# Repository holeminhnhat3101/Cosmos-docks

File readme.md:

# Cosmos Docks

Cosmos Docks is a custom 9-key macropad designed from scratch for Hack Club Stardance. It includes a custom PCB, a fully 3D-printable case, one rotary encoder, an OLED display, and SK6812MINI-E addressable RGB LEDs.

The design is built around the Seeed XIAO RP2040 and uses QMK firmware.

## Features

- 9 MX-style mechanical switches
- 1 EC11 rotary encoder
- 0.91 inch 128×32 I2C OLED display
- 13 SK6812MINI-E addressable RGB LEDs
- Seeed XIAO RP2040 microcontroller
- Custom 2-layer PCB designed in KiCad
- Fully 3D-printable top and bottom case
- QMK firmware with OLED, encoder, and RGB Matrix support
- M3 screws and heat-set inserts for case assembly

### PCB design preview

### PCB Layout

### Schematic

### 3D Assembly

## Bill of Materials

| Component                         | Quantity | Notes                                                              |
| --------------------------------- | -------: | ------------------------------------------------------------------ |
| Seeed XIAO RP2040                 |        1 | Main microcontroller                                               |
| MX-style mechanical switches      |        9 | Main key switches                                                  |
| Blank DSA keycaps                 |        9 | Keycaps for the switches                                           |
| 1N4148W SMD diodes                |        9 | One diode per switch                                               |
| EC11 rotary encoder               |        1 | 20 mm D-shaft rotary encoder                                       |
| 0.91 inch 128×32 I2C OLED display |        1 | OLED screen connected through I2C                                  |
| JST-SH 4-pin connector            |        1 | QWIIC/I2C OLED connector, SM04B-SRSS-TB, 1.00 mm pitch, horizontal |
| SK6812MINI-E RGB LEDs             |       13 | Addressable RGB LEDs                                               |
| 0.1 µF capacitors                 |       13 | One decoupling capacitor per RGB LED                               |
| 10 nF capacitors                  |        2 | Rotary encoder debounce/filtering capacitors                       |
| SN74LV1T34DBV level shifter       |        1 | Shifts LED data from 3.3 V to 5 V                                  |
| 330 Ω resistor                    |        1 | LED data line resistor                                             |
| 10 kΩ resistors                   |        4 | Rotary encoder pull-up/pull-down resistors                         |
| M3×16 mm screws                   |        4 | Used to connect the top and bottom case                            |
| M3 heat-set inserts               |        4 | Installed into the 3D-printed case                                 |
| Custom PCB                        |        1 | 2-layer PCB designed in KiCad                                      |
| 3D-printed top case               |        1 | Top enclosure / switch plate                                       |
| 3D-printed bottom case            |        1 | Bottom enclosure                                                   |
| Soldering equipment               |        1 | I don't have one                                                   |

## Firmware

The firmware is written using QMK. It includes support for:

- 3×3 key matrix
- Rotary encoder
- OLED display
- RGB Matrix lighting for SK6812MINI-E LEDs

The compiled firmware file is included in the production folder as:

firmware.uf2

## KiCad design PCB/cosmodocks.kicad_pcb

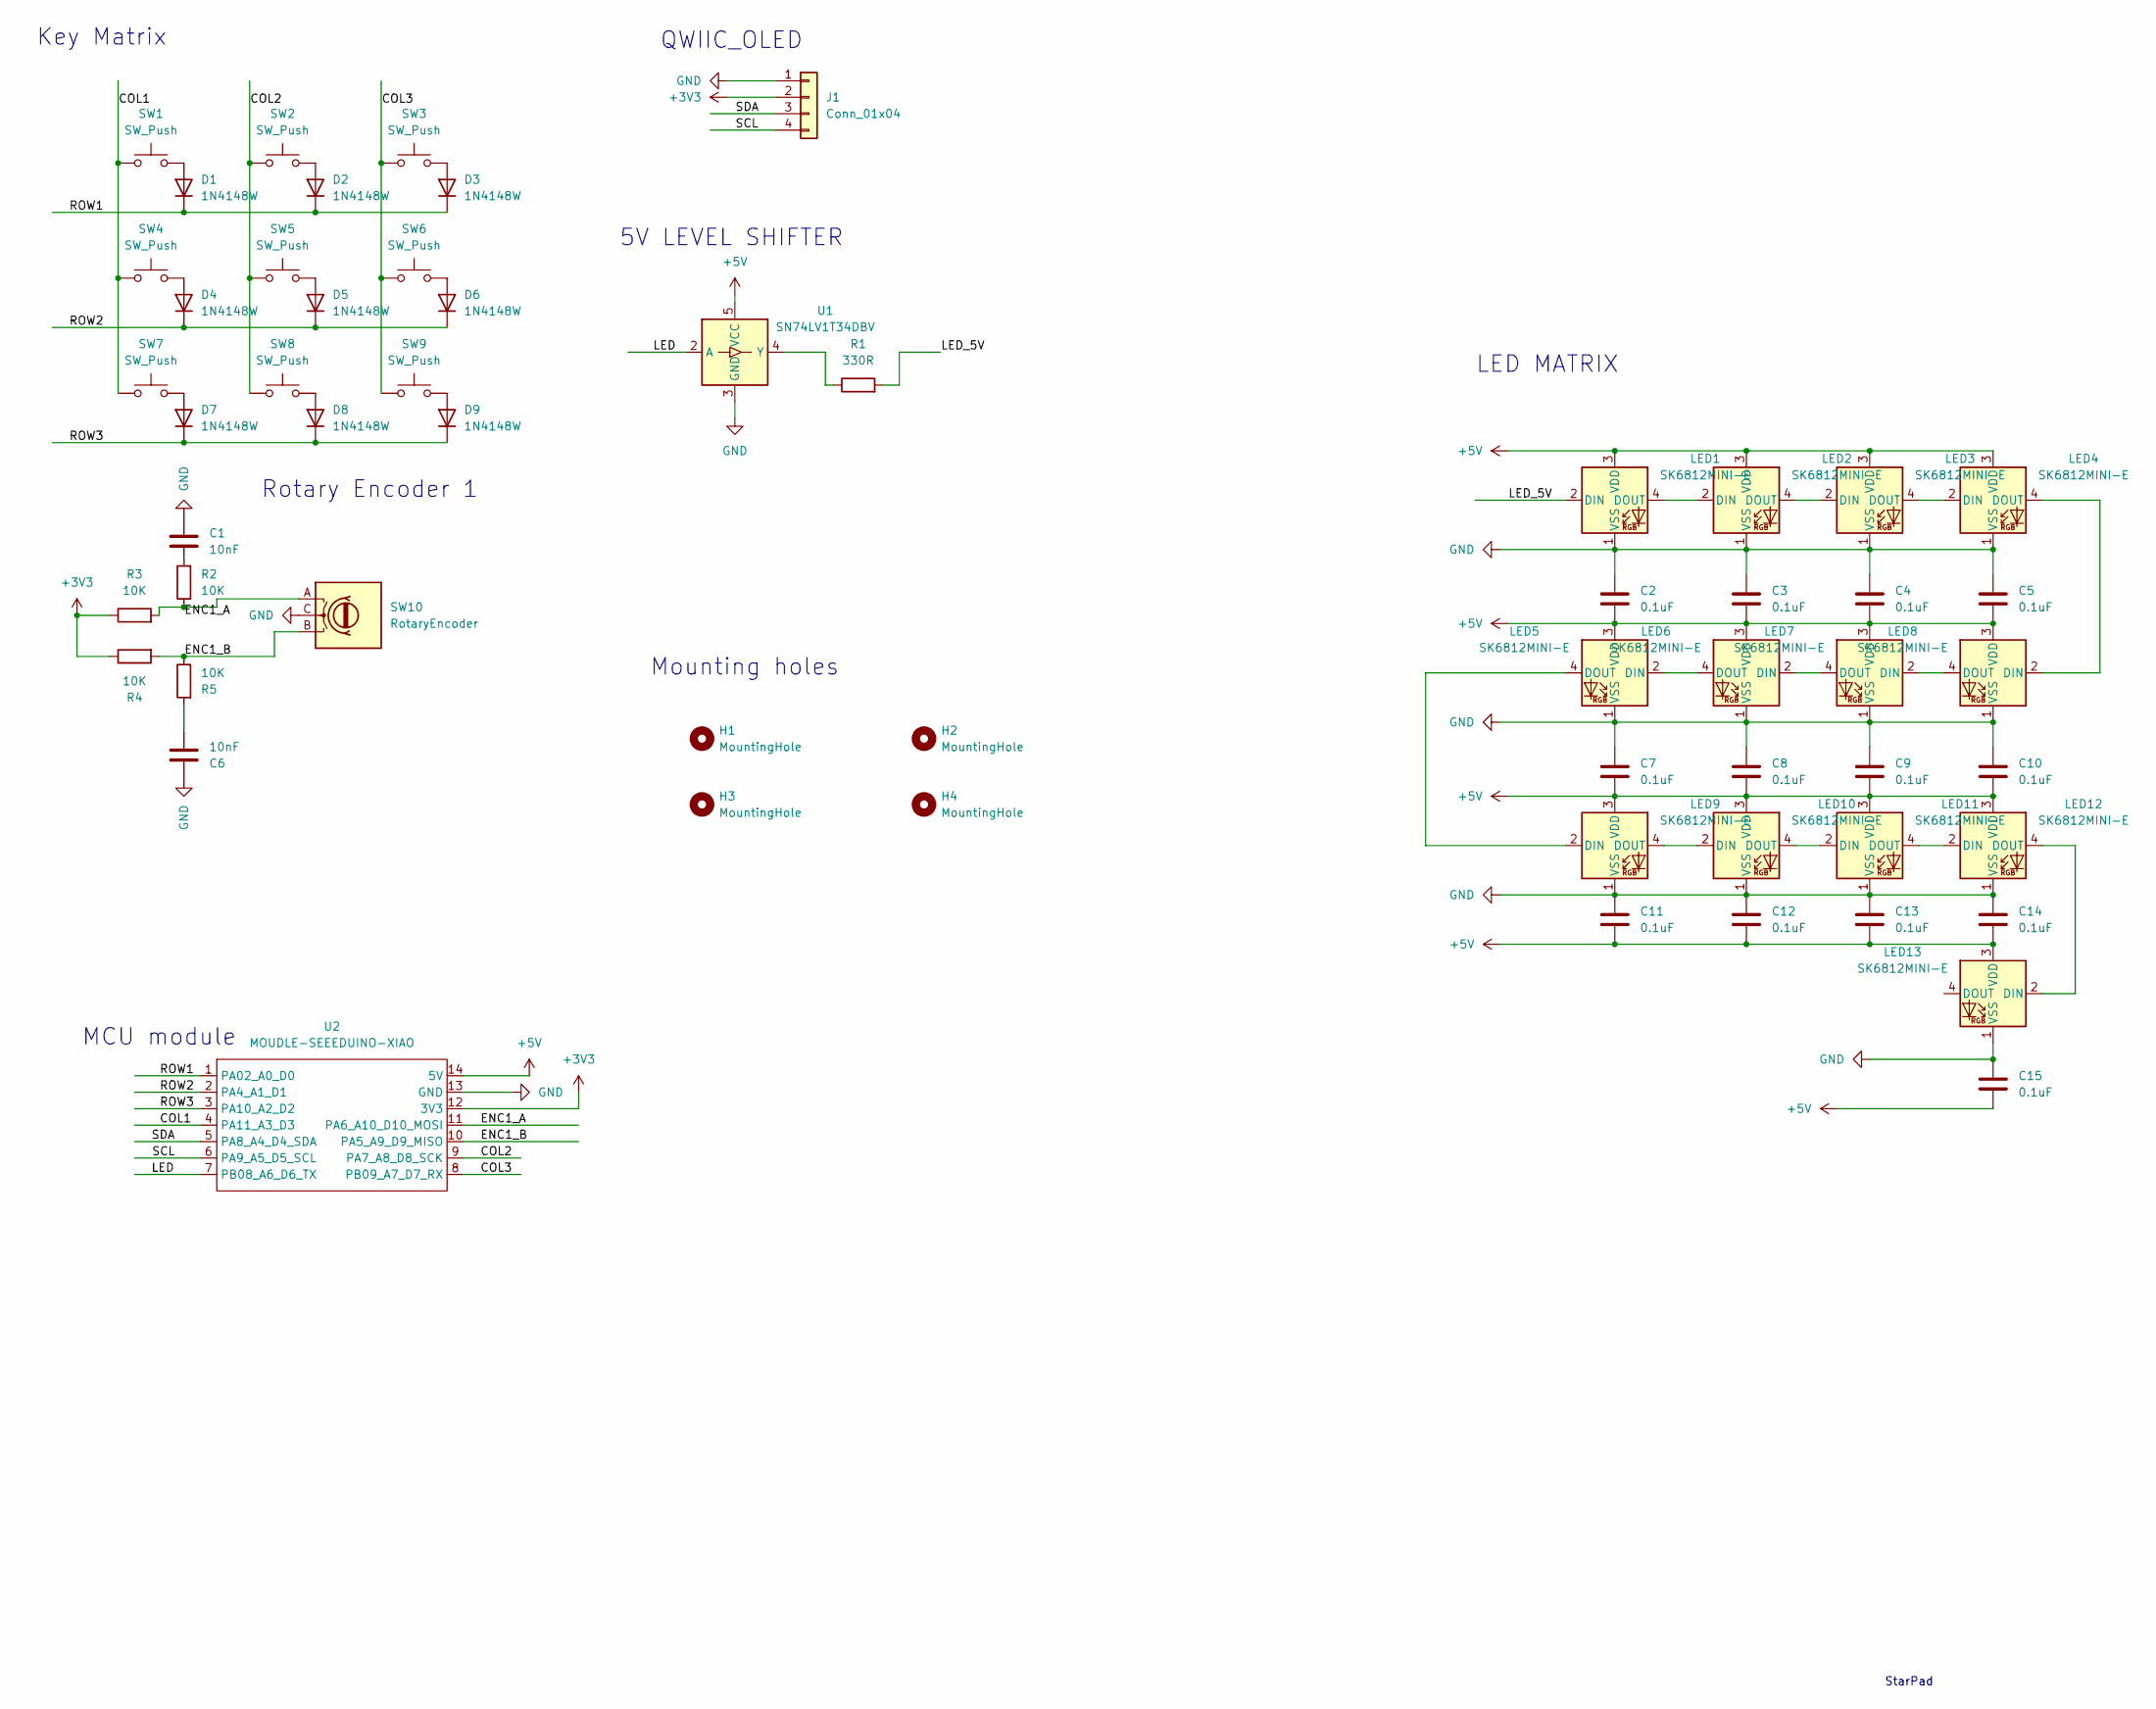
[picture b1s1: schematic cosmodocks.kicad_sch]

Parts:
C1, C6: 10nF; C_0603_1608Metric
C2, C3, C4, C5, C7, C8, C9, C10, C11, C12, C13, C14, C15: 0.1uF; C_0603_1608Metric
D1, D2, D3, D4, D5, D6, D7, D8, D9: 1N4148W; D_SOD-123
H1, H2, H3, H4: MountingHole; MountingHole_2.2mm_M2
J1: Conn_01x04; JST_SH_SM04B-SRSS-TB_1x04-1MP_P1.00mm_Horizontal
LED1, LED2, LED3, LED4, LED5, LED6, LED7, LED8, LED9, LED10, LED11, LED12, LED13: SK6812MINI-E; LED_SK6812MINI-E_3.2x2.8mm_P1.5mm_ReverseMount
R1: 330R; C_0603_1608Metric
R2, R3, R4, R5: 10K; R_0603_1608Metric
SW1, SW2, SW3, SW4, SW5, SW6, SW7, SW8, SW9: SW_Push; SW_Cherry_MX_1.00u_PCB
SW10: RotaryEncoder; RotaryEncoder_Alps_EC11E-Switch_Vertical_H20mm
U1: SN74LV1T34DBV; SOT-23-5
U2: MOUDLE-SEEEDUINO-XIAO; XIAO-Generic-Hybrid-14P-2.54-21X17.8MM

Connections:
+3V3: J1.2, R3.1, R4.1, U2.12 (3V3)
+5V: C2.2, C3.2, C4.2, C5.2, C7.2, C8.2, C9.2, C10.2, C11.2, C12.2, C13.2, C14.2, C15.2, LED1.3 (VDD), LED2.3 (VDD), LED3.3 (VDD), LED4.3 (VDD), LED5.3 (VDD), LED6.3 (VDD), LED7.3 (VDD), LED8.3 (VDD), LED9.3 (VDD), LED10.3 (VDD), LED11.3 (VDD), LED12.3 (VDD), LED13.3 (VDD), U1.5 (VCC), U2.14 (5V)
/COL1: SW1.1, SW4.1, SW7.1, U2.4 (PA11_A3_D3)
/COL2: SW2.1, SW5.1, SW8.1, U2.9 (PA7_A8_D8_SCK)
/COL3: SW3.1, SW6.1, SW9.1, U2.8 (PB09_A7_D7_RX)
/ENC1_A: R2.1, R3.2, SW10.A, U2.11 (PA6_A10_D10_MOSI)
/ENC1_B: R4.2, R5.1, SW10.B, U2.10 (PA5_A9_D9_MISO)
/LED: U1.2 (A), U2.7 (PB08_A6_D6_TX)
/LED_5V: LED1.2 (DIN), R1.2
/ROW1: D1.1 (K), D2.1 (K), D3.1 (K), U2.1 (PA02_A0_D0)
/ROW2: D4.1 (K), D5.1 (K), D6.1 (K), U2.2 (PA4_A1_D1)
/ROW3: D7.1 (K), D8.1 (K), D9.1 (K), U2.3 (PA10_A2_D2)
/SCL: J1.4, U2.6 (PA9_A5_D5_SCL)
/SDA: J1.3, U2.5 (PA8_A4_D4_SDA)
GND: C1.1, C2.1, C3.1, C4.1, C5.1, C6.1, C7.1, C8.1, C9.1, C10.1, C11.1, C12.1, C13.1, C14.1, C15.1, J1.1, LED1.1 (VSS), LED2.1 (VSS), LED3.1 (VSS), LED4.1 (VSS), LED5.1 (VSS), LED6.1 (VSS), LED7.1 (VSS), LED8.1 (VSS), LED9.1 (VSS), LED10.1 (VSS), LED11.1 (VSS), LED12.1 (VSS), LED13.1 (VSS), SW10.C, U1.3 (GND), U2.13 (GND)
unnamed: C1.2, R2.2
unnamed: C6.2, R5.2
unnamed: D1.2 (A), SW1.2
unnamed: D2.2 (A), SW2.2
unnamed: D3.2 (A), SW3.2
unnamed: D4.2 (A), SW4.2
unnamed: D5.2 (A), SW5.2
unnamed: D6.2 (A), SW6.2
unnamed: D7.2 (A), SW7.2
unnamed: D8.2 (A), SW8.2
unnamed: D9.2 (A), SW9.2
unnamed: LED1.4 (DOUT), LED2.2 (DIN)
unnamed: LED2.4 (DOUT), LED3.2 (DIN)
unnamed: LED3.4 (DOUT), LED4.2 (DIN)
unnamed: LED4.4 (DOUT), LED8.2 (DIN)
unnamed: LED5.2 (DIN), LED6.4 (DOUT)
unnamed: LED5.4 (DOUT), LED9.2 (DIN)
unnamed: LED6.2 (DIN), LED7.4 (DOUT)
unnamed: LED7.2 (DIN), LED8.4 (DOUT)
unnamed: LED9.4 (DOUT), LED10.2 (DIN)
unnamed: LED10.4 (DOUT), LED11.2 (DIN)
unnamed: LED11.4 (DOUT), LED12.2 (DIN)
unnamed: LED12.4 (DOUT), LED13.2 (DIN)
unnamed: R1.1, U1.4 (Y)

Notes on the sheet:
Mounting holes
QWIIC_OLED
StarPad
Rotary Encoder 1
LED MATRIX
MCU module
Key Matrix
5V LEVEL SHIFTER

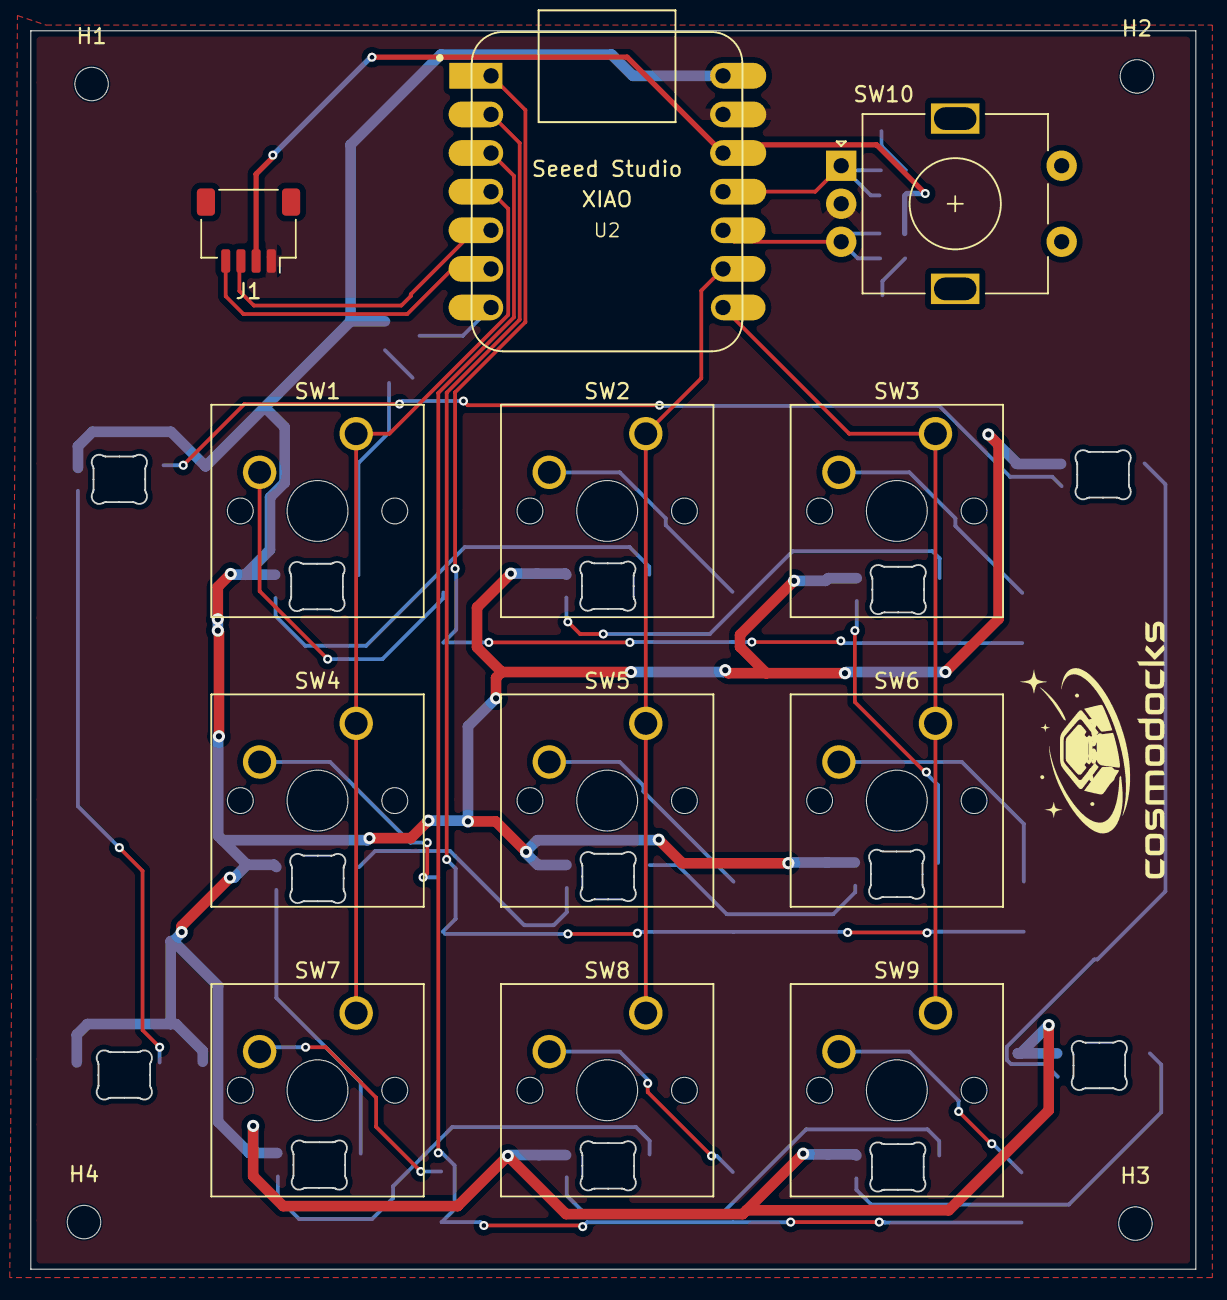
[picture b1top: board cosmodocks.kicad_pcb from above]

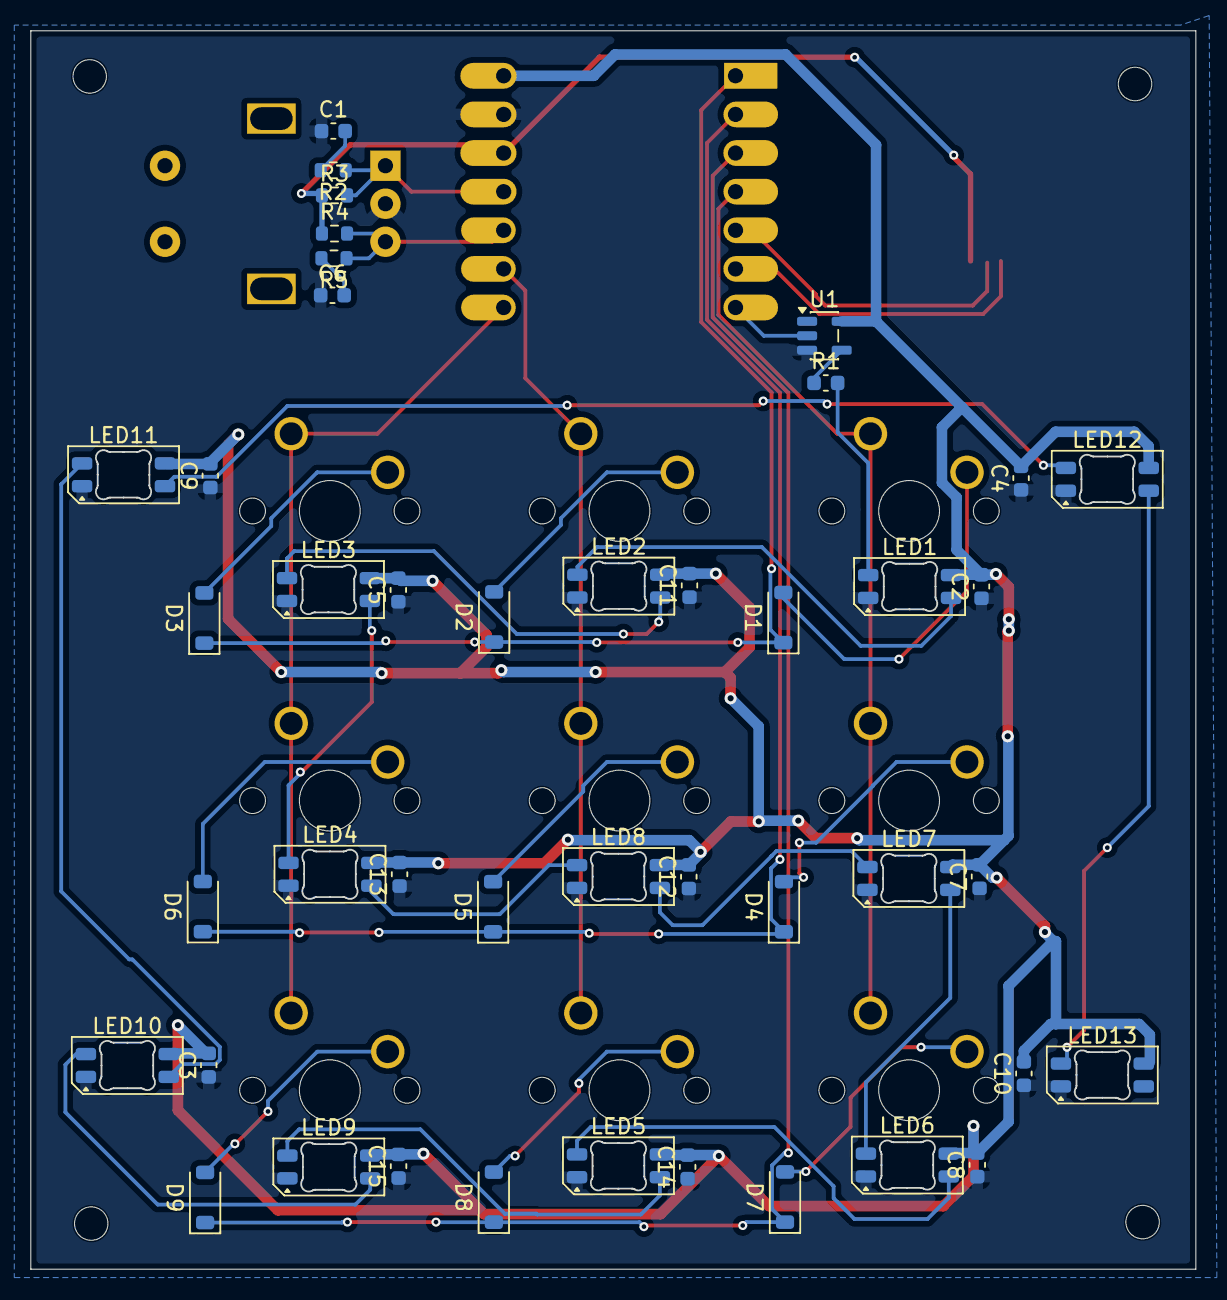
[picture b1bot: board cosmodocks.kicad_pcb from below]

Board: 2 copper layers, 76.6 x 81.5 mm, 59 parts (43 on the bottom side), 39 nets.

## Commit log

2026-06-16 Update copyright holder in LICENSE file
2026-06-16 Updated readme file
